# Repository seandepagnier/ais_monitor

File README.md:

This project is intended to create a simple device that monitors ship traffic and gps location
to sound audible alarms if there is potential for a collision.

It is inspired by the author's experience colliding with a cargo ship while under sail many
miles offshore in deep water.  Despite collision regulations regarding sail vs powered vessels,
commercial ships often do not keep an active watch, and do not set their radar to detect sailboats.

The primary AIS antenna had failed, and the author was very tired from many hours without sleep.
The intention is to create a reliable redundant backup alarm system with an internal 10 hour battery
to ensure an alarm will be heard even in the event of power failure.

The design uses a dAISy receiver coupled with a raspberry pi pico W.  The schematic provides isolated powersupply,
and maintains the battery at a standby level that does not greatly age the battery.   There is an external
speaker.  The nmea streams can be easily accesed via a tcp socket once the pi pico is connected to a wifi network.

free software targeting micropython performs all the calculations and functions and can be easily modified

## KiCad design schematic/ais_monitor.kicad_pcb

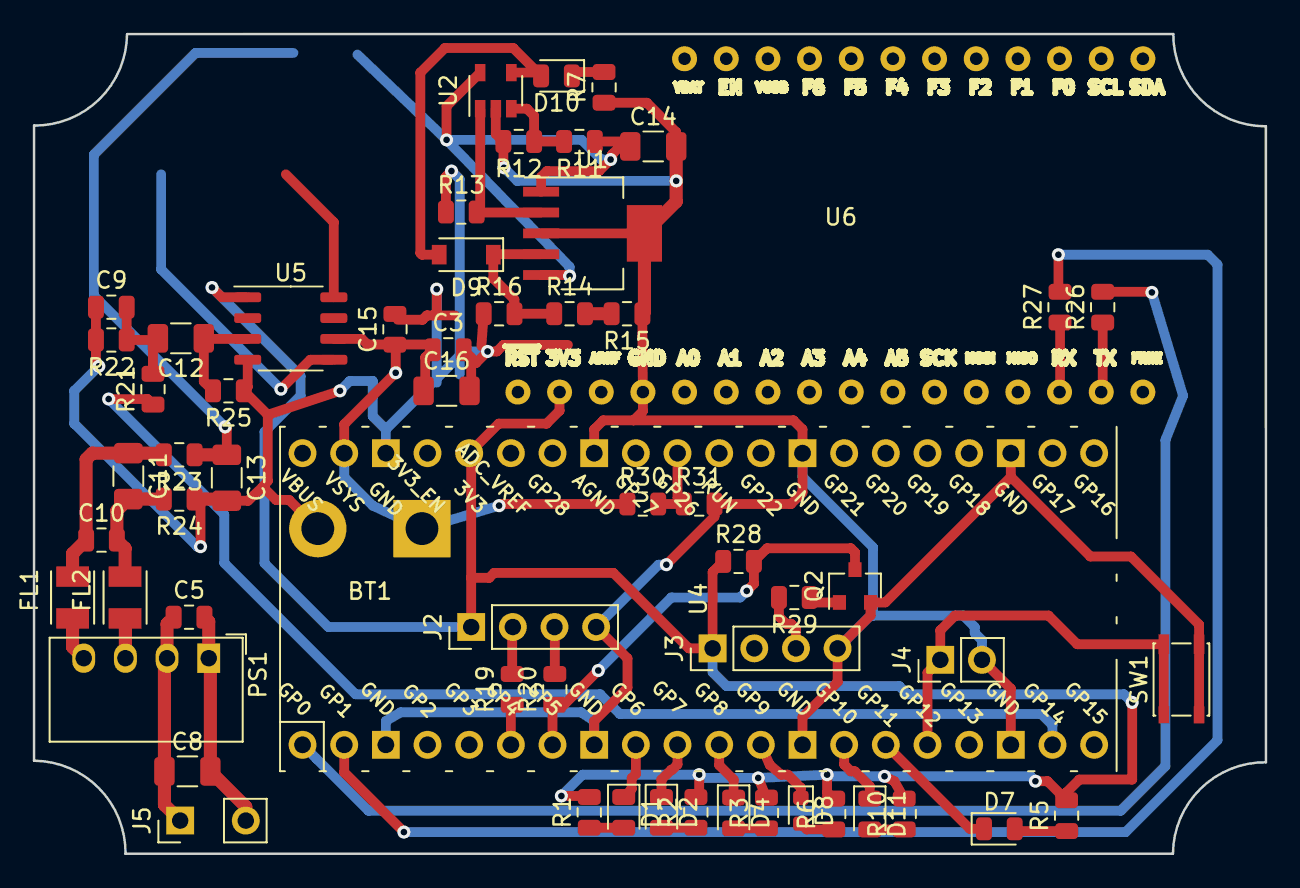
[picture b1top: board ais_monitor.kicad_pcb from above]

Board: 2 copper layers, 75.1 x 50.0 mm, 60 parts (0 on the bottom side), 43 nets.

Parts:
BT1: Battery; SolderWirePad_1x02_P7.62mm_Drill2mm
C3: 1u; C_0805_2012Metric
C5, C9, C10, C15: 100n; C_0805_2012Metric
C8, C11, C12, C13, C14, C16: 10u; C_1206_3216Metric
D1: PWR; LED_0805_2012Metric
D2: AIS; LED_0805_2012Metric
D4: GPS; LED_0805_2012Metric
D7: MUTE; LED_0805_2012Metric
D8: SHIPS; LED_0603_1608Metric
D9: D; D_SOD-123
D10: CHARGE; LED_0805_2012Metric
D11: OWNSHIP; LED_0805_2012Metric
FL1, FL2: NFZ32BW151HN11L; FIL_NFZ32BW151HN11L
J2: GPS; PinHeader_1x04_P2.54mm_Vertical
J3: GPS RS232; PinHeader_1x04_P2.54mm_Vertical
J4: mute; PinHeader_1x02_P2.54mm_Vertical
J5: IN5; PinHeader_1x02_P2.54mm_Vertical
PS1: HLK-PM03; Converter_DCDC_muRata_CRE1xxxxxx3C_THT
Q2: Q_NMOS_DGS; SOT-23
R1, R5, R7, R19, R20, R26, R27, R28, R29: 2k4; R_0805_2012Metric
R2, R3, R6, R10: 1k2; R_0805_2012Metric
R11: 10k; R_0805_2012Metric
R12, R30, R31: 100k; R_0805_2012Metric
R13: 4.7; R_0805_2012Metric
R14: 20k; R_0805_2012Metric
R15, R25: 1k; R_0805_2012Metric
R16: 47k; R_0805_2012Metric
R21, R22: 100; R_0805_2012Metric
R23, R24: 1; R_0805_2012Metric
SW1: Mute; SW_SPST_PTS810
U1: TPS73701; SOT-223-6_TabPin3
U2: LM321; SOT-23-5
U4: Pico; RPi_Pico_SMD_TH
U5: PAM8302AAD; SOP-8_3.9x4.9mm_P1.27mm
U6: feather

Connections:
+3V3: J2.1, J3.1, R1.2, R2.2, R3.2, R5.2, R6.2, R10.2, R28.1, U4.36, U5.1, U6.14
+5V: C13.1, C14.1, R11.1, R23.1, U1.1, U1.5, U2.5
+BATT: BT1.1, C3.1, C15.1, C16.1, R13.1, R16.1, R30.1, U4.39, U5.6
AIS: D2.1, U4.10
GND: BT1.2, C3.2, C9.1, C13.2, C14.2, C15.2, C16.2, J2.4, J3.4, J4.2, Q2.2, R7.1, R12.2, R15.1, R22.2, R24.1, R25.1, R31.2, SW1.2, U1.3, U2.2, U4.3, U4.8, U4.13, U4.18, U4.23, U4.28, U4.33, U4.38, U5.4, U5.7, U6.16
GPS: D4.1, U4.11
MUTE: D7.1, U4.15
MUTEB: J4.1, SW1.1, U4.16
unnamed: C5.2, C8.2, J5.2, PS1.1
unnamed: C5.1, C8.1, J5.1, PS1.2
unnamed: C10.1, C11.1, FL1.2, R23.2
unnamed: C10.2, C11.2, FL2.2, R24.2
unnamed: C12.1, R25.2, U5.3
unnamed: C9.2, C12.2, R21.2, R22.1
unnamed: D1.2, R1.1
unnamed: D2.2, R2.1
unnamed: D4.2, R3.1
unnamed: D7.2, R5.1
unnamed: D8.2, R6.1
unnamed: D9.1, R14.1, R16.2, U1.4
unnamed: D10.1, R7.2
unnamed: D9.2, D10.2, U2.4
unnamed: D11.2, R10.1
unnamed: FL1.1, PS1.4
unnamed: FL2.1, PS1.3
unnamed: J2.2, R19.2
unnamed: J2.3, R20.2
unnamed: J3.3, R29.2
unnamed: Q2.1, R29.1
unnamed: R11.2, R12.1, U2.3
unnamed: R13.2, U1.2, U2.1
unnamed: R14.2, R15.2
unnamed: R21.1, U4.19
unnamed: R26.1, U6.27
unnamed: R27.1, U6.26
unnamed: R30.2, R31.1, U4.31
OWNSHIP: D11.1, U4.14
PWR: D1.1, U4.9
RX0: R27.2, U4.2
RX1: Q2.3, R20.1, R28.2, U4.7
SHIPS: D8.1, U4.12
TX0: R26.2, U4.1
TX1: R19.1, U4.6

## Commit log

2024-02-24 more updates
2024-02-24 add boot
2024-03-15 many updates
